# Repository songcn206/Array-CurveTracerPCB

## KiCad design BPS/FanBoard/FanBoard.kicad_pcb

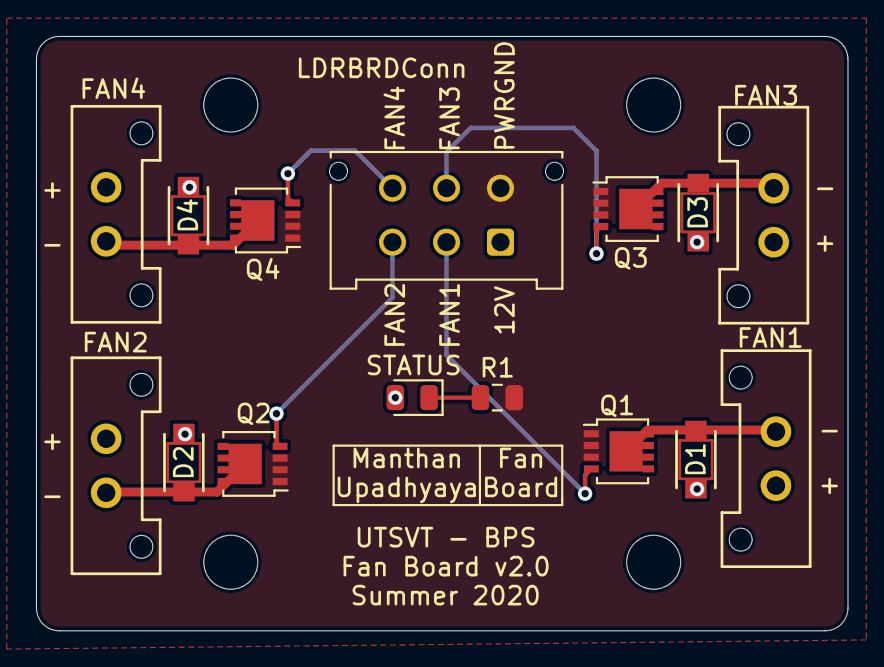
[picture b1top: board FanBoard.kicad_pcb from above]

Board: 2 copper layers, 45.1 x 33.0 mm, 19 parts (0 on the bottom side), 11 nets.

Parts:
D1, D2, D3, D4: V2F22HM
FAN1: FAN1; Molex_MicroFit3.0_1x2xP3.00mm_PolarizingPeg_Vertical
FAN2: FAN2; Molex_MicroFit3.0_1x2xP3.00mm_PolarizingPeg_Vertical
FAN3: FAN3; Molex_MicroFit3.0_1x2xP3.00mm_PolarizingPeg_Vertical
FAN4: FAN4; Molex_MicroFit3.0_1x2xP3.00mm_PolarizingPeg_Vertical
H1, H2, H3, H4: MountingHole; MountingHole_3mm
LDRBRDConn: LDRBRDConn; Molex_Micro-Fit_3.0_43045-0612_2x03_P3.00mm_Vertical
Q1, Q2, Q3, Q4: BUK9M34-100EX; LFPAK33
R1: 45k; R_0805_2012Metric
STATUS: LED; LED_0805_2012Metric

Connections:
+12V: D1.1, D2.1, D3.1, D4.1, FAN1.1, FAN2.1, FAN3.1, FAN4.1, LDRBRDConn.1, STATUS.2
/FAN1: LDRBRDConn.2, Q1.4
/FAN2: LDRBRDConn.3, Q2.4
/FAN3: LDRBRDConn.5, Q3.4
/FAN4: LDRBRDConn.6, Q4.4
GNDPWR: LDRBRDConn.4, Q1.1, Q1.2, Q1.3, Q2.1, Q2.2, Q2.3, Q3.1, Q3.2, Q3.3, Q4.1, Q4.2, Q4.3, R1.2
unnamed: D1.2, FAN1.2, Q1.5
unnamed: D2.2, FAN2.2, Q2.5
unnamed: D3.2, FAN3.2, Q3.5
unnamed: D4.2, FAN4.2, Q4.5
unnamed: R1.1, STATUS.1

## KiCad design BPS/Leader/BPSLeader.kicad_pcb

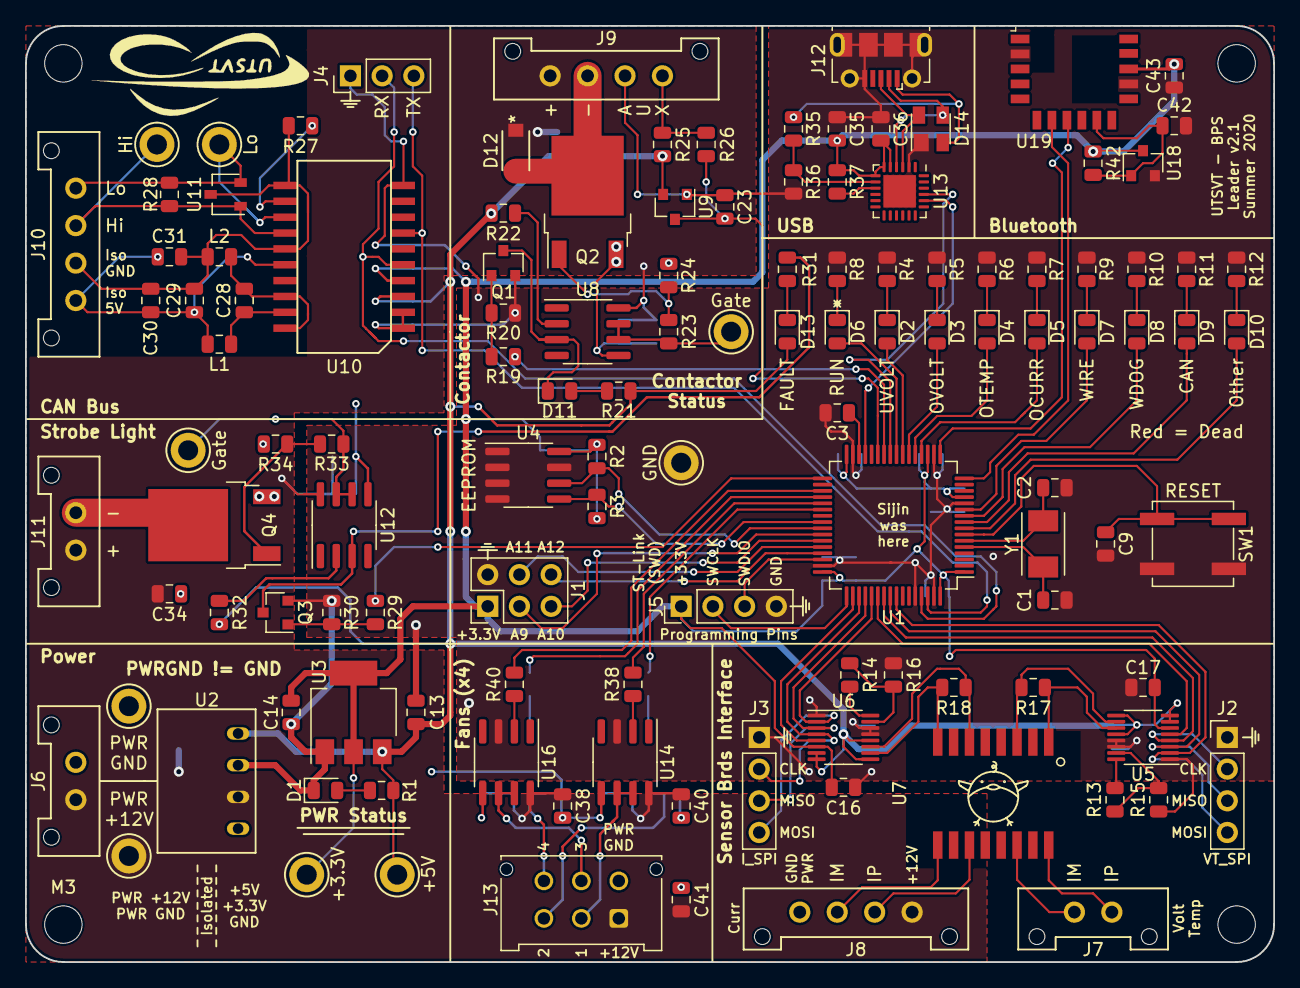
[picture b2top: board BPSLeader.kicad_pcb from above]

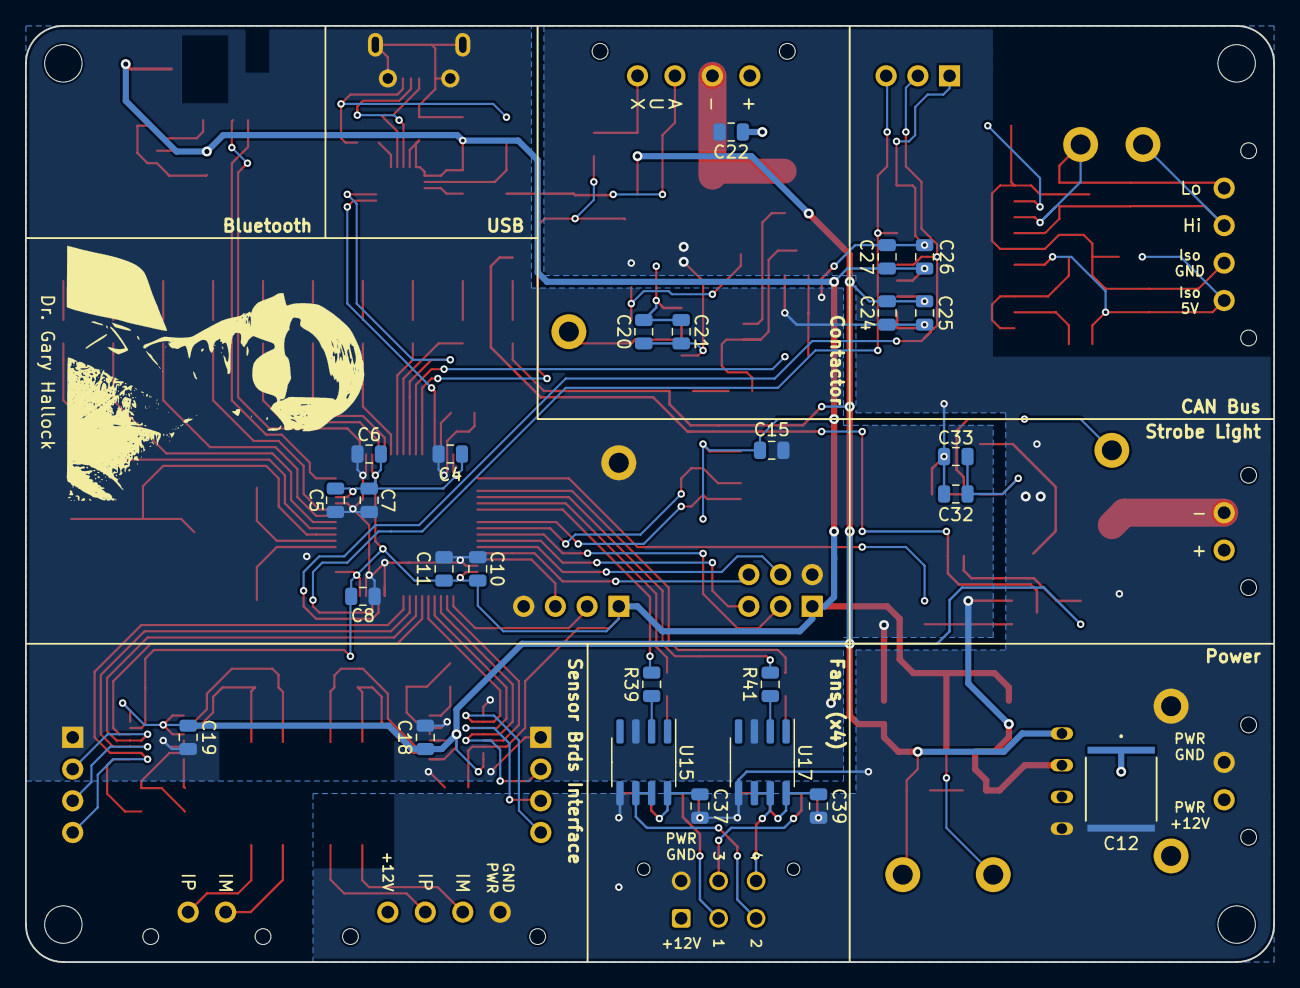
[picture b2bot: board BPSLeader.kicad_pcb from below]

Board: 2 copper layers, 100.0 x 75.0 mm, 154 parts (27 on the bottom side), 105 nets.

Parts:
C1, C2: 10p; C_0805_2012Metric
C3, C11, C35: 4.7u; C_0805_2012Metric
C4, C5, C6, C8, C9, C10, C15, C16, C17, C18, C19, C20, C25, C26, C30, C32, C36, C37, C38, C39, C40, C43: 0.1u; C_0805_2012Metric
C7, C22, C23, C34, C42: 1u; C_0805_2012Metric
C12: 10u; C_2220_5750Metric
C13, C14, C21, C24, C29, C33, C41: 10u; C_0805_2012Metric
C27, C31: 0.01u; C_0805_2012Metric
C28: 0.22u; C_0805_2012Metric
D1: PowerOn; LED_0805_2012Metric
D2: UVolt; LED_0805_2012Metric
D3: OVolt; LED_0805_2012Metric
D4: OTemp; LED_0805_2012Metric
D5: OCurr; LED_0805_2012Metric
D6: Heartbeat; LED_0805_2012Metric
D7: Wire; LED_0805_2012Metric
D8: WDError; LED_0805_2012Metric
D9: CANError; LED_0805_2012Metric
D10: Other; LED_0805_2012Metric
D11: ContactorEn; LED_0805_2012Metric
D12: V2F22HM3/H; V2F22HM
D13: Fault; LED_0805_2012Metric
D14: SP0503BAHT; SOT-143
J1: GPIO Analyzer; PinHeader_2x03_P2.54mm_Vertical
J2: Volt/Temp SPI Analyzer; PinHeader_1x04_P2.54mm_Vertical
J3: Current SPI Analyzer; PinHeader_1x04_P2.54mm_Vertical
J4: CAN Analyzer; PinHeader_1x03_P2.54mm_Vertical
J5: SWD; PinHeader_1x04_P2.54mm_Vertical
J6: PowerConn; Molex_MicroFit3.0_1x2xP3.00mm_PolarizingPeg_Vertical
J7: MinionConn; Molex_MicroFit3.0_1x2xP3.00mm_PolarizingPeg_Vertical
J8: CurrentConn; Molex_MicroFit3.0_1x4xP3.00mm_PolarizingPeg_Vertical
J9: ContactorConn; Molex_MicroFit3.0_1x4xP3.00mm_PolarizingPeg_Vertical
J10: CAN_Out; Molex_MicroFit3.0_1x4xP3.00mm_PolarizingPeg_Vertical
J11: ErrorLightConn; Molex_MicroFit3.0_1x2xP3.00mm_PolarizingPeg_Vertical
J12: USB_B_Micro; USB_Micro-B_Molex-105017-0001
J13: FanBrdConn; Molex_Micro-Fit_3.0_43045-0612_2x03_P3.00mm_Vertical
L1, L2: 2k; L_0805_2012Metric
LOGO1: Dr. Hallock; Hallock_Image_Small
LOGO2: UTSVT Logo; UTSVT_Logo_Symbol
MH1, MH2, MH3, MH4: M.3; MountingHole_3mm
Q1, Q3: NTR4003NT1G; SOT-23
Q2, Q4: VND5N07-E; TO-252-2
R1, R21: 1.5k; R_0805_2012Metric
R2, R3, R25, R42: 4.7k; R_0805_2012Metric
R4, R5, R6, R7, R9, R10, R11, R12: 750; R_0805_2012Metric
R8: 680; R_0805_2012Metric
R13, R14: 806; R_0805_2012Metric
R15, R16: 1.21k; R_0805_2012Metric
R17, R18, R28: 120; R_0805_2012Metric
R19, R23, R27, R29, R33: 0; R_0805_2012Metric
R20, R24, R30, R34: 10k; R_0805_2012Metric
R22, R32: 470; R_0805_2012Metric
R26, R37: 1k; R_0805_2012Metric
R31: 1.6k; R_0805_2012Metric
R35: 22.1k; R_0805_2012Metric
R36: 47.5k; R_0805_2012Metric
R38, R39, R40, R41: 117; R_0805_2012Metric
SW1: B3SL-1002P; SW_SPST_B3SL-1002P
TP1: +12V_TP; TestPoint_Keystone_5005-5009_Compact
TP2: GNDPWR_TP; TestPoint_Keystone_5005-5009_Compact
TP3: +5V_TP; TestPoint_Keystone_5005-5009_Compact
TP4: GND_TP; TestPoint_Keystone_5005-5009_Compact
TP5: +3.3V_TP; TestPoint_Keystone_5005-5009_Compact
TP6: ContactorGate_TP; TestPoint_Keystone_5005-5009_Compact
TP7: CAN_H; TestPoint_Keystone_5005-5009_Compact
TP8: CAN_L; TestPoint_Keystone_5005-5009_Compact
TP9: StrobeLightGate_TP; TestPoint_Keystone_5005-5009_Compact
U1: STM32F413RHTx; LQFP-64_10x10mm_P0.5mm
U2: RI3-1205S; RI3_DC_Converter
U3: NCP1117-3.3_SOT223; SOT-223-3_TabPin2
U4: M24128; SOIC-8_3.9x4.9mm_P1.27mm
U5, U6: LTC6820; MSOP-16_3x4mm_P0.5mm
U7: HX1188FNL; HXXXX
U8, U12, U14, U15, U16, U17: SI8261ABC-IS; SOIC-8_3.9x4.9mm_P1.27mm
U9: BAS70-04; SOT-23
U10: ADM3055E; SOIC-20W_7.5x15.4mm_Pitch1.27mm
U11: CDSOT23-T24CAN; SOT-23W
U13: CP2102N-A01-GQFN24; QFN-24-1EP_4x4mm_P0.5mm_EP2.6x2.6mm
U18: MCP112; SOT-23
U19: RN4871-I; Microchip_RN4871
Y1: 8M; Crystal_SMD_TXC_7A-2Pin_5x3.2mm

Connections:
+3V3: C4.1, C5.1, C6.1, C7.1, C8.1, C10.1, C11.1, C14.1, C15.1, C16.1, C17.1, C26.1, C27.1, C35.1, C36.1, C43.2, J1.1, J5.1, R2.1, R3.1, R37.1, R42.1, TP5.1, U1.1, U1.13, U1.19, U1.32, U1.48, U1.64, U3.2, U4.8, U5.6, U6.6, U10.4, U13.5, U13.6, U13.7, U18.3, U19.14
+5V: C13.1, C18.1, C19.1, C24.1, C25.1, D13.2, R1.1, R21.1, R22.2, R25.2, R32.2, TP3.1, U2.4, U3.3, U5.7, U5.8, U5.9, U5.12, U6.7, U6.8, U6.9, U6.12, U9.2, U10.3
+12V: C12.1, C20.1, C21.1, C22.2, C32.1, C33.1, C34.2, C37.1, C38.1, C39.1, C40.1, C41.1, D12.1, J6.1, J8.1, J9.1, J11.1, J13.1, TP1.1, U2.2, U8.8, U12.8, U14.8, U15.8, U16.8, U17.8
/CAN1_RX: J4.2, U1.61, U10.5
/CAN1_TX: J4.3, U1.62, U10.7
/CAN/CAN_H: J10.3, R28.2, TP7.1, U10.14, U11.1
/CAN/CAN_L: J10.4, R28.1, TP8.1, U10.13, U11.2
/CAN/RSlope: R27.1, U10.12
/Contactor Driver/CONTACTOR_V-: D12.2, J9.2, Q2.2
/FAULT: R29.2, U1.33
/Fan Board Interface/FAN1: J13.2, U14.6, U14.7
/Fan Board Interface/FAN2: J13.3, U15.6, U15.7
/Fan Board Interface/FAN3: J13.5, U16.6, U16.7
/Fan Board Interface/FAN4: J13.6, U17.6, U17.7
/I2C3_SCL: R2.2, U1.41, U4.6
/I2C3_SDA: R3.2, U1.40, U4.5
/NRST: C9.1, SW1.1, U1.7
/OSC_IN: C1.1, U1.5, Y1.1
/OSC_OUT: C2.1, U1.6, Y1.2
/PA4: D5.2, U1.20
/PA5: D4.2, U1.21
/PA6: D3.2, U1.22
/PA7: D2.2, U1.23
/PA9: J1.3, U1.42
/PA10: J1.5, U1.43
/PA11: J1.4, U1.44
/PA12: J1.6, U1.45
/PA15: U1.50, U6.5
/PB0: R19.2, U1.26
/PB1: C23.1, R26.1, U1.27, U9.3
/PC0: D10.2, U1.8
/PC1: D9.2, U1.9
/PC2: D8.2, U1.10
/PC3: D7.2, U1.11
/PC4: D6.2, U1.24
/PD2: U1.54, U5.5
/SPI1_CLK: J2.2, U1.55, U5.4
/SPI1_MISO: J2.3, U1.56, U5.3
/SPI1_MOSI: J2.4, U1.57, U5.2
/SPI3_CLK: J3.2, U1.51, U6.4
/SPI3_MISO: J3.3, U1.52, U6.3
/SPI3_MOSI: J3.4, U1.53, U6.2
/SWCLK: J5.2, U1.49
/SWDIO: J5.3, U1.46
/Sensor Boards Interface/I_IM: R18.2, U6.10, U7.8
/Sensor Boards Interface/I_IP: R18.1, U6.11, U7.6
/Sensor Boards Interface/VT_IM: R17.2, U5.10, U7.3
/Sensor Boards Interface/VT_IP: R17.1, U5.11, U7.1
/TIM3_CH1: R38.2, U1.37
/TIM3_CH2: R39.2, U1.38
/TIM12_CH1: R40.2, U1.35
/TIM12_CH2: R41.2, U1.36
/UART2_RX: U1.17, U19.8
/UART2_TX: U1.16, U19.7
/USART3_RX: U1.25, U13.21
/USART3_TX: U1.29, U13.20
GND: C1.2, C2.2, C3.2, C4.2, C5.2, C6.2, C7.2, C8.2, C9.2, C10.2, C11.2, C13.2, C14.2, C15.2, C16.2, C17.2, C18.2, C19.2, C23.2, C24.2, C25.2, C26.2, C27.2, C35.2, C36.2, C42.2, C43.1, D1.1, D14.1, J1.2, J2.1, J3.1, J4.1, J5.4, J9.3, J12.5, J12.6, Q1.2, Q3.2, R4.2, R5.2, R6.2, R7.2, R8.2, R9.2, R10.2, R11.2, R12.2, R15.1, R16.1, R20.2, R30.2, R36.2, SW1.2, TP4.1, U1.12, U1.18, U1.31, U1.47, U1.60, U1.63, U2.3, U3.1, U4.1, U4.2, U4.3, U4.4, U4.7, U5.1, U5.13, U5.14, U6.1, U6.13, U6.14, U9.1, U10.1, U10.2, U10.10, U13.2, U13.25, U14.3, U15.3, U16.3, U17.3, U18.2, U19.2, U19.13
GNDPWR: C12.2, C20.2, C21.2, C22.1, C32.2, C33.2, C34.1, C37.2, C38.2, C39.2, C40.2, C41.2, J6.2, J8.4, J13.4, Q2.3, Q4.3, R24.2, R34.2, TP2.1, U2.1, U8.5, U12.5, U14.5, U15.5, U16.5, U17.5
unnamed: C3.1, U1.30
unnamed: C28.1, L1.2, U10.19
unnamed: C28.2, L2.2, U10.18, U10.20
unnamed: C29.1, C30.1, C31.1, J10.1, L1.1, U10.16
unnamed: C29.2, C30.2, C31.2, J10.2, L2.1, R27.2, U10.11, U10.15, U11.3
unnamed: C42.1, R42.2, U18.1, U19.10
unnamed: D1.2, R1.2
unnamed: D2.1, R4.1
unnamed: D3.1, R5.1
unnamed: D4.1, R6.1
unnamed: D5.1, R7.1
unnamed: D6.1, R8.1
unnamed: D7.1, R9.1
unnamed: D8.1, R10.1
unnamed: D9.1, R11.1
unnamed: D10.1, R12.1
unnamed: D11.1, Q1.3, U8.3
unnamed: D11.2, R21.2
unnamed: D13.1, R31.1
unnamed: D14.2, J12.1, R35.2
unnamed: D14.3, J12.2, U13.4
unnamed: D14.4, J12.3, U13.3
unnamed: J7.1, U7.16
unnamed: J7.2, U7.14
unnamed: J8.2, U7.11
unnamed: J8.3, U7.9
unnamed: J9.4, R25.1, R26.2
unnamed: J11.2, Q4.2
unnamed: Q1.1, R19.1, R20.1
unnamed: Q2.1, R23.1, R24.1
unnamed: Q3.1, R29.1, R30.1
unnamed: Q3.3, R31.2, U12.3
unnamed: Q4.1, R33.1, R34.1
unnamed: R13.1, R15.2, U5.15
unnamed: R13.2, U5.16
unnamed: R14.1, R16.2, U6.15
unnamed: R14.2, U6.16
unnamed: R22.1, U8.2
unnamed: R23.2, TP6.1, U8.6, U8.7
unnamed: R32.1, U12.2
unnamed: R33.2, TP9.1, U12.6, U12.7
unnamed: R35.1, R36.1, U13.8
unnamed: R37.2, U13.9
unnamed: R38.1, U14.2
unnamed: R39.1, U15.2
unnamed: R40.1, U16.2
unnamed: R41.1, U17.2

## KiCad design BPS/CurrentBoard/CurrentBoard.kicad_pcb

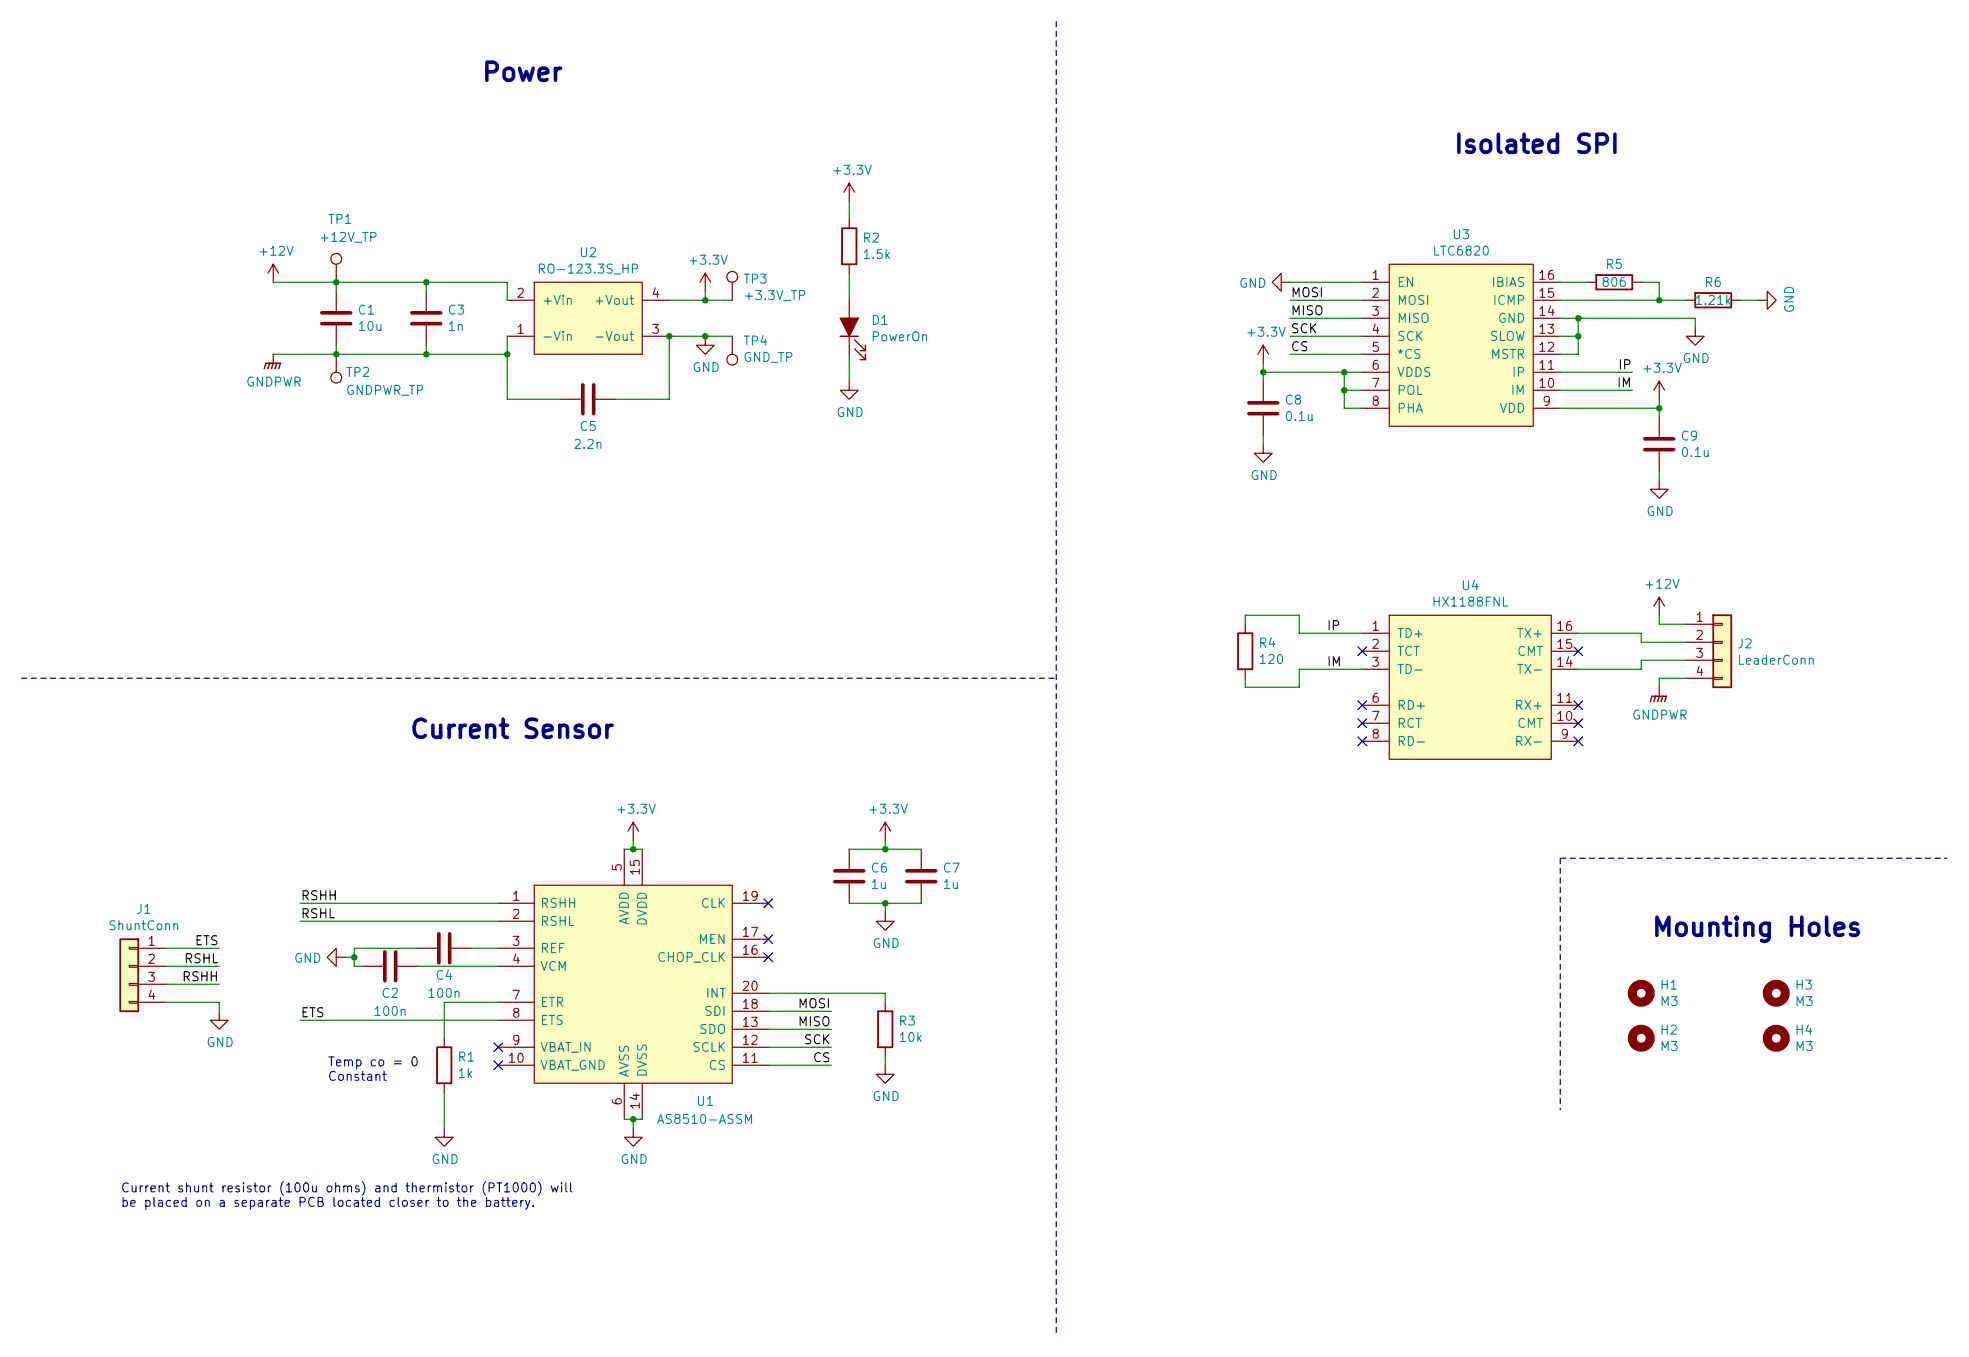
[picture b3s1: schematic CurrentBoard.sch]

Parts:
C1: 10u; C_2220_5750Metrix
C2, C4: 100n; C_0805_2012Metric
C3: 1n; C_0805_2012Metric
C5: 2.2n; C_0805_2012Metric
C6, C7: 1u; C_0805_2012Metric
C8, C9: 0.1u; C_0805_2012Metric
D1: PowerOn; LED_0805_2012Metric
H1, H2, H3, H4: M3; MountingHole_3mm
J1: ShuntConn; Molex_Micro-Fit_3.0_43650-0415_1x04_P3.00mm_Vertical
J2: LeaderConn; Molex_Micro-Fit_3.0_43650-0415_1x04_P3.00mm_Vertical
R1: 1k; R_0805_2012Metric
R2: 1.5k; R_0805_2012Metric
R3: 10k; R_0805_2012Metric
R4: 120; R_0805_2012Metric
R5: 806; R_0805_2012Metric
R6: 1.21k; R_0805_2012Metric
TP1: +12V_TP; TestPoint_Keystone_5005-5009_Compact
TP2: GNDPWR_TP; TestPoint_Keystone_5005-5009_Compact
TP3: +3.3V_TP; TestPoint_Keystone_5005-5009_Compact
TP4: GND_TP; TestPoint_Keystone_5005-5009_Compact
U1: AS8510-ASSM; Manufacturer_Part_Number AS8510-ASSM; Mouser Part Number 985-AS8510-ASSM
U2: RO-123.3S_HP; RI3_DC_Converter
U3: LTC6820; MSOP-16_3x4mm_P0.5mm
U4: HX1188FNL; HXXXX

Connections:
+3V3: C6.1, C7.1, C8.1, C9.1, R2.1, TP3.1, U1.5 (AVDD), U1.15 (DVDD), U2.4 (+Vout), U3.6 (VDDS), U3.7 (POL), U3.8 (PHA), U3.9 (VDD)
+12V: C1.1, C3.1, J2.1, TP1.1, U2.2 (+Vin)
/CS: U1.11 (CS), U3.5 (*CS)
/ETS: J1.1, U1.8 (ETS)
/IM: R4.2, U3.10 (IM), U4.3 (TD-)
/IP: R4.1, U3.11 (IP), U4.1 (TD+)
/MISO: U1.13 (SDO), U3.3 (MISO)
/MOSI: U1.18 (SDI), U3.2 (MOSI)
/RSHH: J1.3, U1.1 (RSHH)
/RSHL: J1.2, U1.2 (RSHL)
/SCK: U1.12 (SCLK), U3.4 (SCK)
GND: C2.2, C4.1, C5.2, C6.2, C7.2, C8.2, C9.2, D1.1 (K), J1.4, R1.2, R3.2, R6.1, TP4.1, U1.6 (AVSS), U1.14 (DVSS), U2.3 (-Vout), U3.1 (EN), U3.12 (MSTR), U3.13 (SLOW), U3.14 (GND)
GNDPWR: C1.2, C3.2, C5.1, J2.4, TP2.1, U2.1 (-Vin)
unnamed: C2.1, U1.4 (VCM)
unnamed: C4.2, U1.3 (REF)
unnamed: D1.2 (A), R2.2
unnamed: J2.2, U4.16 (TX+)
unnamed: J2.3, U4.14 (TX-)
unnamed: R1.1, U1.7 (ETR)
unnamed: R3.1, U1.20 (INT)
unnamed: R5.1, R6.2, U3.15 (ICMP)
unnamed: R5.2, U3.16 (IBIAS)

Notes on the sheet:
Current shunt resistor (100u ohms) and thermistor (PT1000) will be placed on a separate PCB located closer to the battery.
Temp co = 0 Constant
Isolated SPI
Current Sensor
Mounting Holes
Power

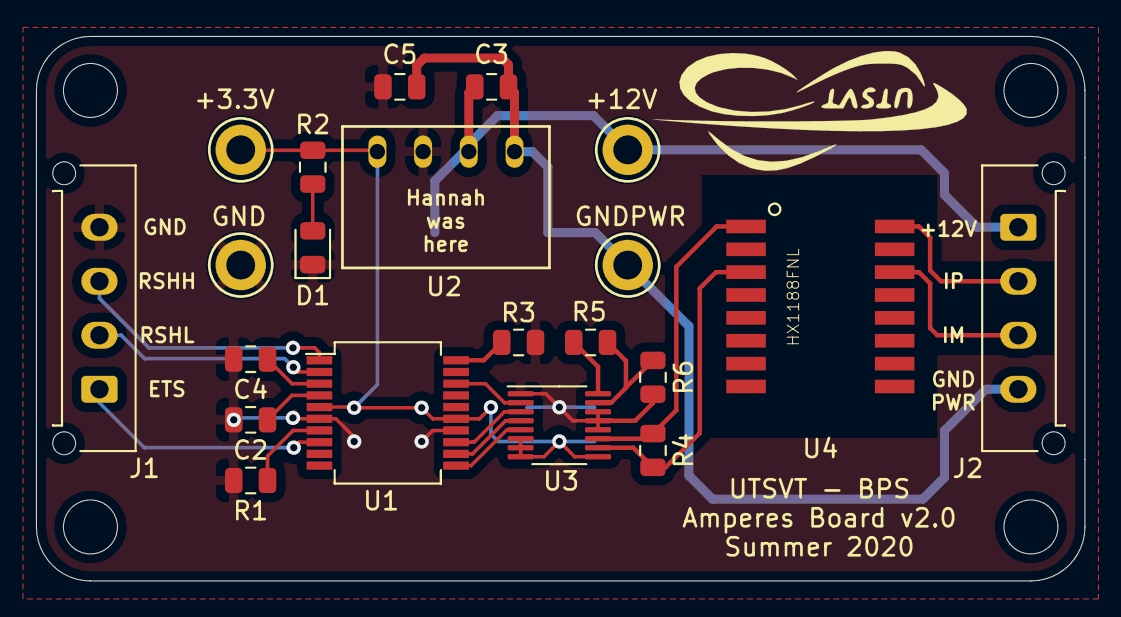
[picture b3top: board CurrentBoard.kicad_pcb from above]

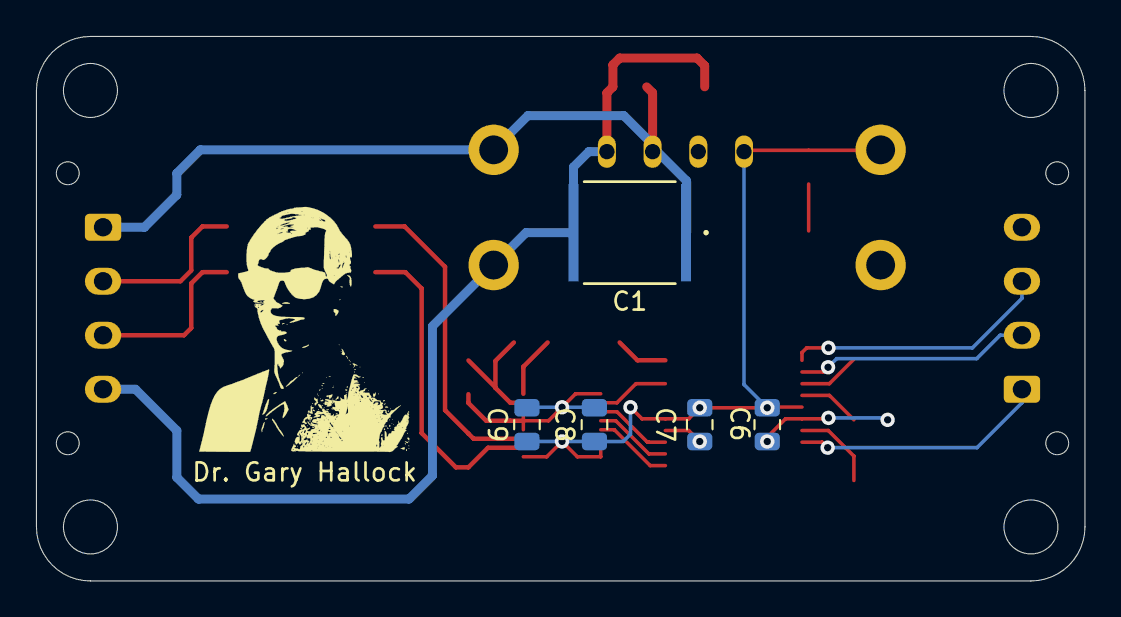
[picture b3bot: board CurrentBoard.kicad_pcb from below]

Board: 2 copper layers, 58.2 x 30.2 mm, 30 parts (5 on the bottom side), 22 nets.

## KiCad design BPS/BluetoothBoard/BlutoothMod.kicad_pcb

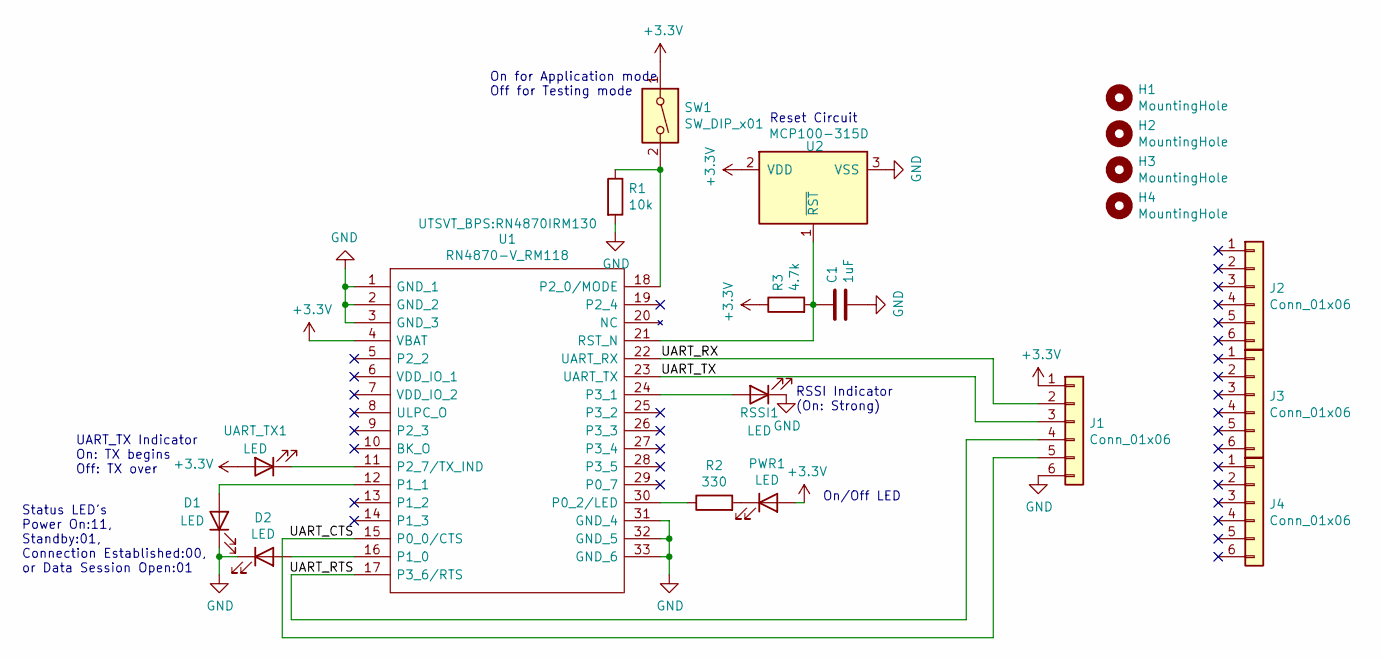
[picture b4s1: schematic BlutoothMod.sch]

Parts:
C1: 1uF; C_0805_2012Metric
D1, D2: LED; LED_0805_2012Metric
H1, H2, H3, H4: MountingHole; MountingHole_2.1mm
J1, J2, J3, J4: Conn_01x06; PinSocket_1x06_P2.54mm_Vertical
PWR1: LED; LED_0805_2012Metric
R1: 10k; R_0805_2012Metric
R2: 330; R_0805_2012Metric
R3: 4.7k; R_0805_2012Metric
RSSI1: LED; LED_0805_2012Metric
SW1: SW_DIP_x01; SW_DIP_SPSTx01_Slide_6.7x4.1mm_W6.73mm_P2.54mm_LowProfile_J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
U1: RN4870-V_RM118; RN4870IRM130; Manufacturer_Part_Number RN4870-V/RM118; Mouser Part Number 579-RN4870-V/RM118
U2: MCP100-315D; SOT96P240X110-3N
UART_TX1: LED; LED_0805_2012Metric

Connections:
+3V3: J1.1, PWR1.2 (A), R3.1, SW1.1, U1.4 (VBAT), U2.2 (VDD), UART_TX1.2 (A)
/UART_CTS: J1.5, U1.15 (P0_0/CTS)
/UART_RTS: J1.4, U1.17 (P3_6/RTS)
/UART_RX: J1.2, U1.22 (UART_RX)
/UART_TX: J1.3, U1.23 (UART_TX)
GND: C1.2, D1.1 (K), D2.1 (K), J1.6, R1.2, RSSI1.1 (K), U1.1 (GND_1), U1.2 (GND_2), U1.3 (GND_3), U1.31 (GND_4), U1.32 (GND_5), U1.33 (GND_6), U2.3 (VSS)
unnamed: C1.1, R3.2, U1.21 (RST_N), U2.1 (~RST)
unnamed: D1.2 (A), U1.12 (P1_1)
unnamed: D2.2 (A), U1.16 (P1_0)
unnamed: PWR1.1 (K), R2.2
unnamed: R1.1, SW1.2, U1.18 (P2_0/MODE)
unnamed: R2.1, U1.30 (P0_2/LED)
unnamed: RSSI1.2 (A), U1.24 (P3_1)
unnamed: U1.11 (P2_7/TX_IND), UART_TX1.1 (K)

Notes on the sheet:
Status LED's Power On:11, Standby:01, Connection Established:00, or Data Session Open:01
On/Off LED
Reset Circuit
RSSI Indicator (On: Strong)
UART_TX Indicator On: TX begins Off: TX over
On for Application mode Off for Testing mode

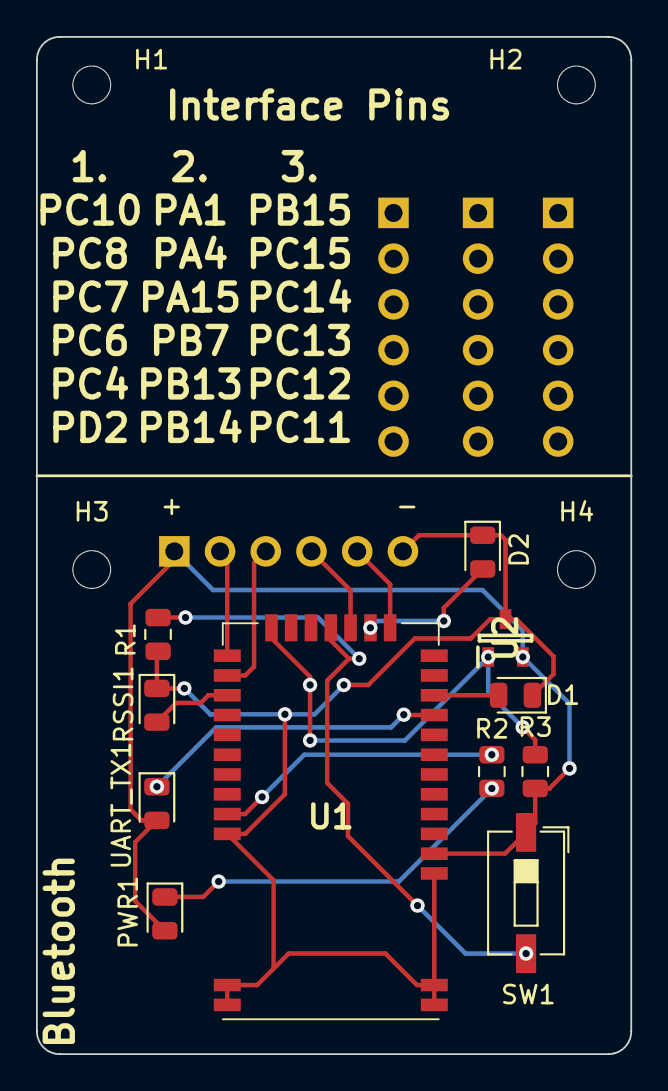
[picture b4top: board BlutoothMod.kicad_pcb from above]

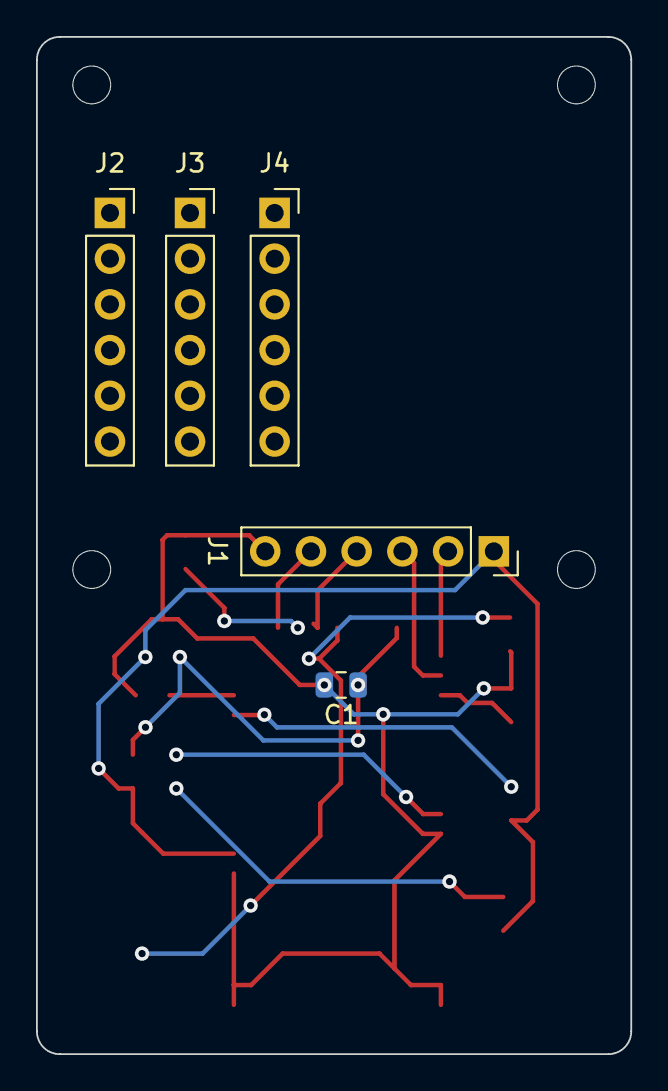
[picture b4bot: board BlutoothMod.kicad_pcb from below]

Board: 2 copper layers, 33.0 x 56.5 mm, 20 parts (5 on the bottom side), 14 nets.

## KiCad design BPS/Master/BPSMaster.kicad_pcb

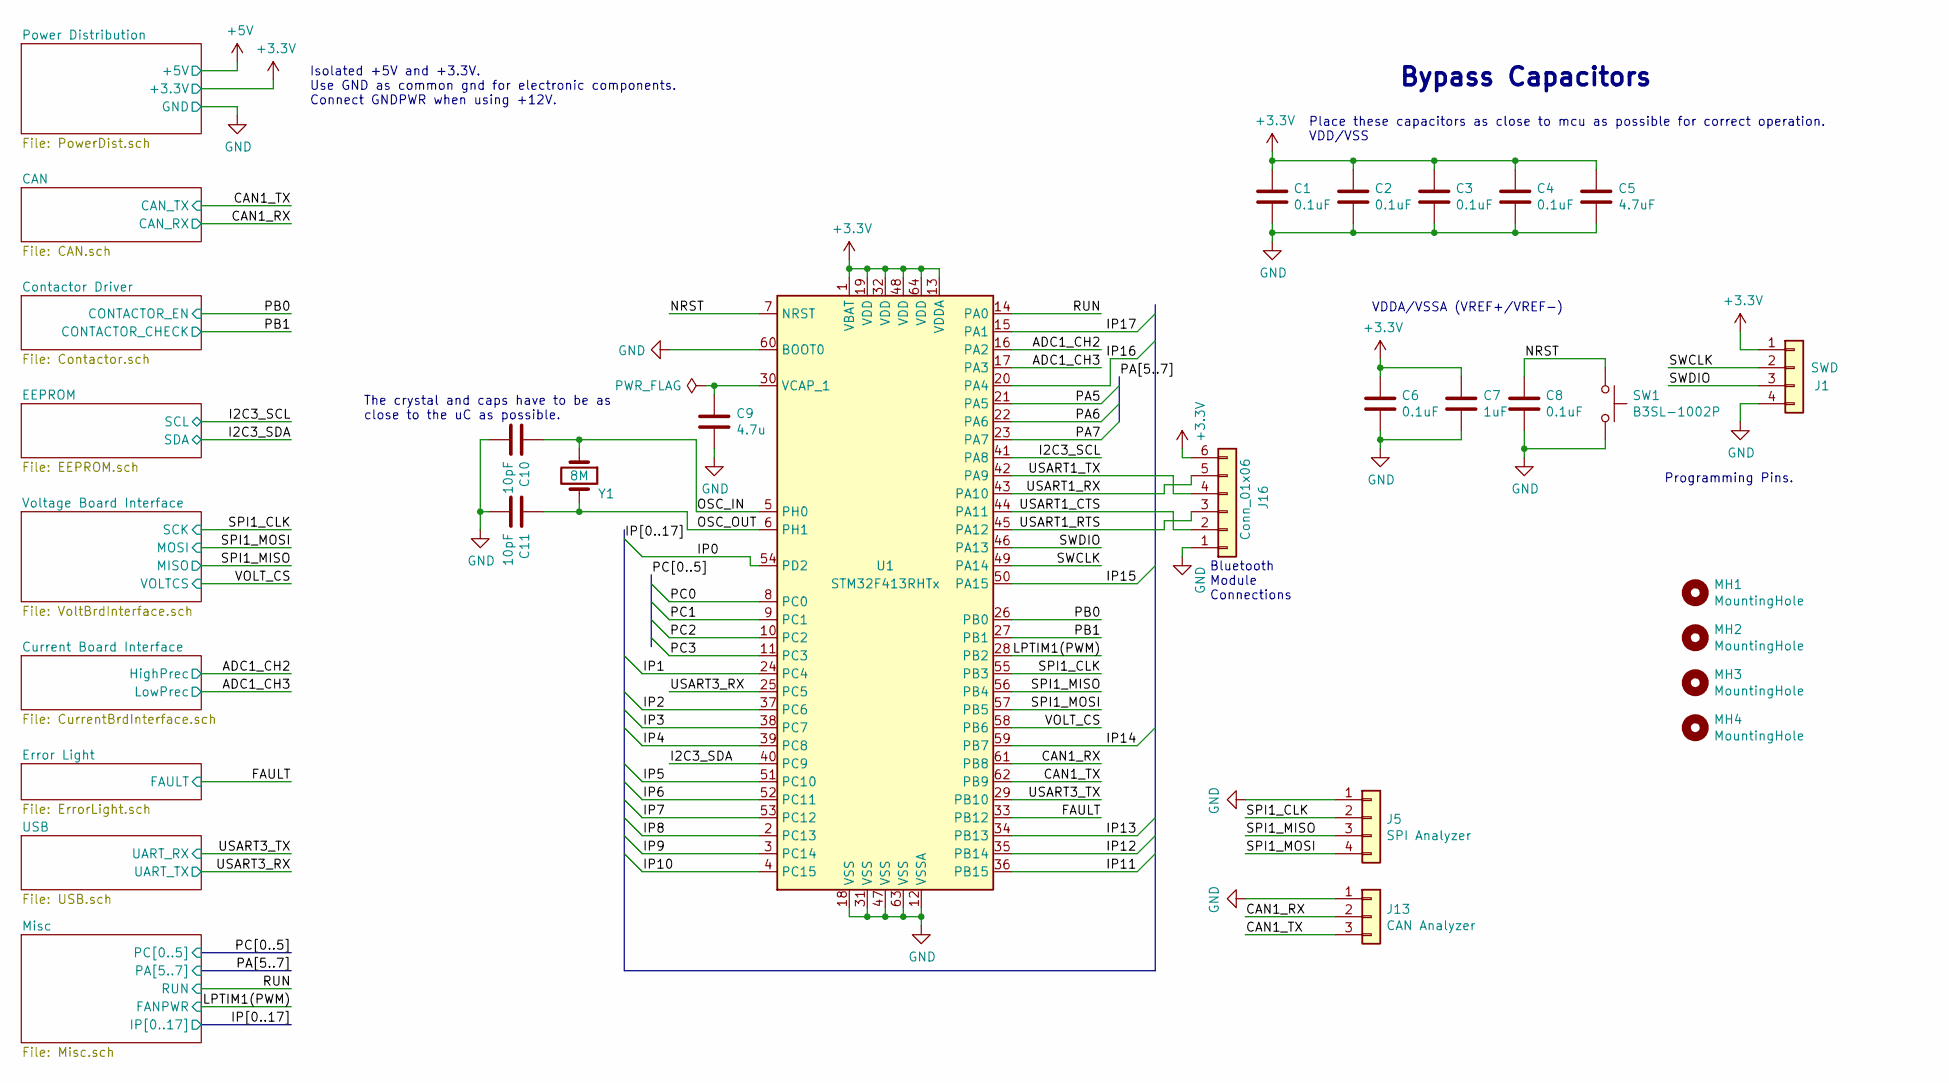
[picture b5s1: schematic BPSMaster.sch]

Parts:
C1, C2, C3, C4, C6, C8: 0.1uF; C_0805_2012Metric
C5: 4.7uF; C_0805_2012Metric
C7: 1uF; C_0805_2012Metric
C9: 4.7u; C_0805_2012Metric
C10, C11: 10pF; C_0805_2012Metric
J1: SWD; PinHeader_1x04_P2.54mm_Vertical
J5: SPI Analyzer; PinHeader_1x04_P2.54mm_Vertical
J13: CAN Analyzer; PinHeader_1x03_P2.54mm_Vertical
J16: Conn_01x06; PinHeader_1x06_P2.54mm_Vertical
MH1, MH2, MH3, MH4: MountingHole; MountingHole_3mm
SW1: B3SL-1002P; SW_SPST_B3SL-1002P
U1: STM32F413RHTx; LQFP-64_10x10mm_P0.5mm
Y1: 8M; Crystal_SMD_TXC_7A-2Pin_5x3.2mm

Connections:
+3V3: C1.1, C2.1, C3.1, C4.1, C5.1, C6.1, C7.1, J1.1, J16.6, U1.1 (VBAT), U1.13 (VDDA), U1.19 (VDD), U1.32 (VDD), U1.48 (VDD), U1.64 (VDD); also elsewhere on the board
/ADC1_CH2: U1.16 (PA2); also elsewhere on the board
/ADC1_CH3: U1.17 (PA3); also elsewhere on the board
/CAN1_RX: J13.2, U1.61 (PB8); also elsewhere on the board
/CAN1_TX: J13.3, U1.62 (PB9); also elsewhere on the board
/FAULT: U1.33 (PB12); also elsewhere on the board
/I2C3_SCL: U1.41 (PA8); also elsewhere on the board
/I2C3_SDA: U1.40 (PC9); also elsewhere on the board
/IP0: U1.54 (PD2); also elsewhere on the board
/IP1: U1.24 (PC4); also elsewhere on the board
/IP2: U1.37 (PC6); also elsewhere on the board
/IP3: U1.38 (PC7); also elsewhere on the board
/IP4: U1.39 (PC8); also elsewhere on the board
/IP5: U1.51 (PC10); also elsewhere on the board
/IP6: U1.52 (PC11); also elsewhere on the board
/IP7: U1.53 (PC12); also elsewhere on the board
/IP8: U1.2 (PC13); also elsewhere on the board
/IP9: U1.3 (PC14); also elsewhere on the board
/IP10: U1.4 (PC15); also elsewhere on the board
/IP11: U1.36 (PB15); also elsewhere on the board
/IP12: U1.35 (PB14); also elsewhere on the board
/IP13: U1.34 (PB13); also elsewhere on the board
/IP14: U1.59 (PB7); also elsewhere on the board
/IP15: U1.50 (PA15); also elsewhere on the board
/IP16: U1.20 (PA4); also elsewhere on the board
/IP17: U1.15 (PA1); also elsewhere on the board
/LPTIM1(PWM): U1.28 (PB2); also elsewhere on the board
/NRST: C8.1, SW1.1, U1.7 (NRST)
/OSC_IN: C10.1, U1.5 (PH0), Y1.1
/OSC_OUT: C11.1, U1.6 (PH1), Y1.2
/PA5: U1.21 (PA5); also elsewhere on the board
/PA6: U1.22 (PA6); also elsewhere on the board
/PA7: U1.23 (PA7); also elsewhere on the board
/PB0: U1.26 (PB0); also elsewhere on the board
/PB1: U1.27 (PB1); also elsewhere on the board
/PC0: U1.8 (PC0); also elsewhere on the board
/PC1: U1.9 (PC1); also elsewhere on the board
/PC2: U1.10 (PC2); also elsewhere on the board
/PC3: U1.11 (PC3); also elsewhere on the board
/RUN: U1.14 (PA0); also elsewhere on the board
/SPI1_CLK: J5.2, U1.55 (PB3); also elsewhere on the board
/SPI1_MISO: J5.3, U1.56 (PB4); also elsewhere on the board
/SPI1_MOSI: J5.4, U1.57 (PB5); also elsewhere on the board
/SWCLK: J1.2, U1.49 (PA14)
/SWDIO: J1.3, U1.46 (PA13)
/USART1_CTS: J16.2, U1.44 (PA11)
/USART1_RTS: J16.3, U1.45 (PA12)
/USART1_RX: J16.5, U1.43 (PA10)
/USART1_TX: J16.4, U1.42 (PA9)
/USART3_RX: U1.25 (PC5); also elsewhere on the board
/USART3_TX: U1.29 (PB10); also elsewhere on the board
/VOLT_CS: U1.58 (PB6); also elsewhere on the board
GND: C1.2, C2.2, C3.2, C4.2, C5.2, C6.2, C7.2, C8.2, C9.2, C10.2, C11.2, J1.4, J5.1, J13.1, J16.1, SW1.2, U1.12 (VSSA), U1.18 (VSS), U1.31 (VSS), U1.47 (VSS), U1.60 (BOOT0), U1.63 (VSS); also elsewhere on the board
unnamed: C9.1, U1.30 (VCAP_1)

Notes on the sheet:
Place these capacitors as close to mcu as possible for correct operation. VDD/VSS
VDDA/VSSA (VREF+/VREF-)
Isolated +5V and +3.3V. Use GND as common gnd for electronic components. Connect GNDPWR when using +12V.
The crystal and caps have to be as close to the uC as possible.
Programming Pins.
Bypass Capacitors
Bluetooth Module Connections

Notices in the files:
parts and their libraries:
Copyright 2016 Accelerated Designs. All rights reserved.
